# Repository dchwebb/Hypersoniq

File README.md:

# Hypersoniq
 Eurorack Polyphonic High Pass Filter

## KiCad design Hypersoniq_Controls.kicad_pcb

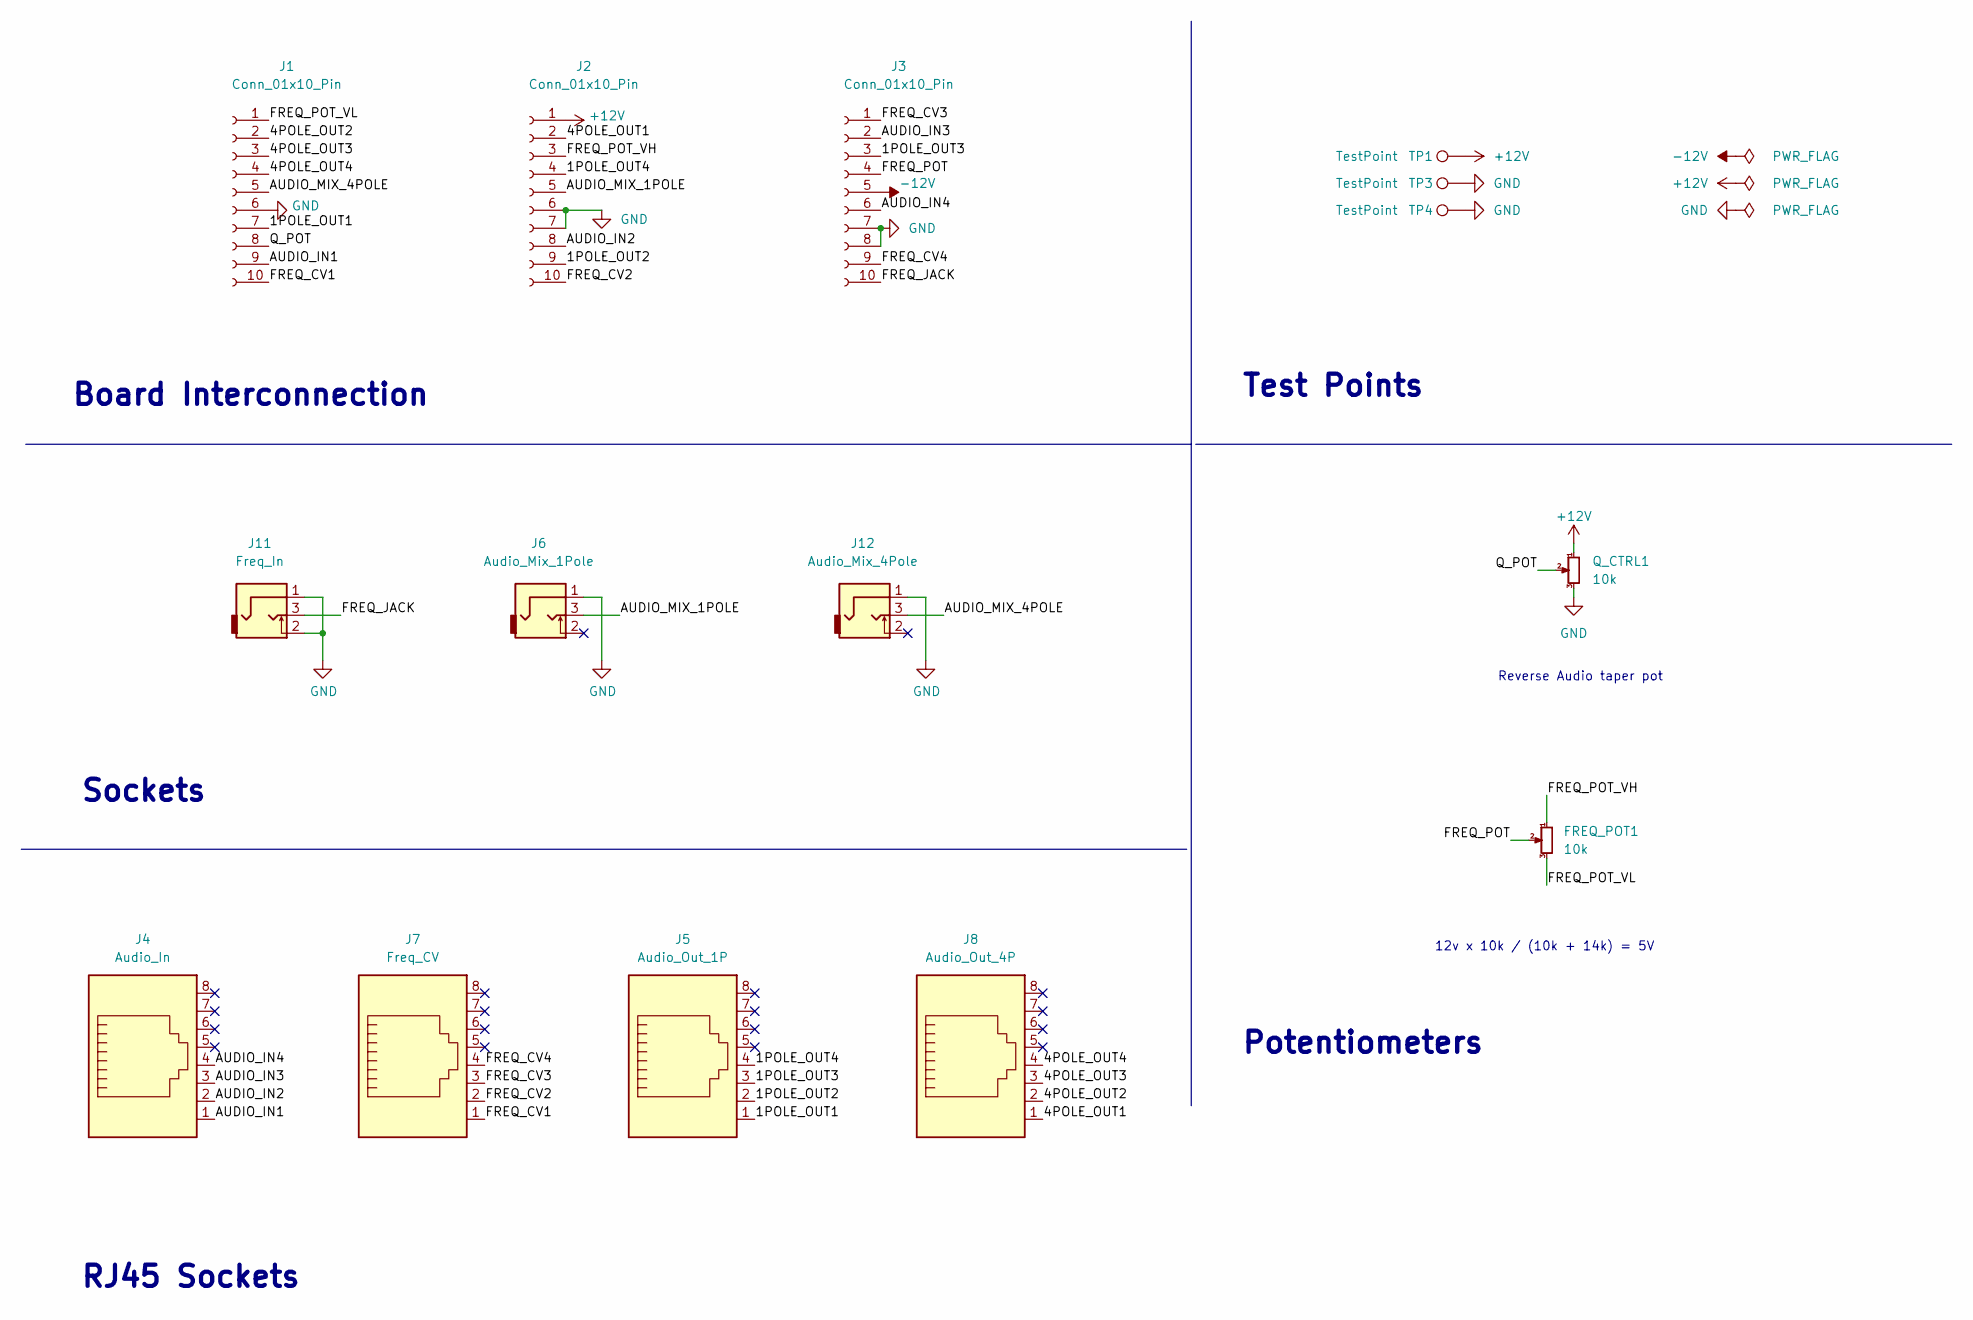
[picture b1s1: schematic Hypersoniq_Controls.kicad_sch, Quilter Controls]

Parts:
FREQ_POT1: 10k; Alpha_9mm_Potentiometer_Aligned
J1, J2, J3: Conn_01x10_Pin; PinSocket_1x10_P2.54mm_Vertical
J4: Audio_In; RJ45_Molex_42878-8506
J5: Audio_Out_1P; RJ45_Molex_42878-8506
J6: Audio_Mix_1Pole; THONKICONN_hole
J7: Freq_CV; RJ45_Molex_42878-8506
J8: Audio_Out_4P; RJ45_Molex_42878-8506
J11: Freq_In; THONKICONN_hole
J12: Audio_Mix_4Pole; THONKICONN_hole
Q_CTRL1: 10k; Alpha_9mm_Potentiometer_Aligned
TP1, TP3, TP4: TestPoint; 1.3mm_Test_Point

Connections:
+12V: J2.1, Q_CTRL1.1, TP1.1
-12V: J3.5
/1POLE_OUT1: J1.7, J5.1
/1POLE_OUT2: J2.9, J5.2
/1POLE_OUT3: J3.3, J5.3
/1POLE_OUT4: J2.4, J5.4
/4POLE_OUT1: J2.2, J8.1
/4POLE_OUT2: J1.2, J8.2
/4POLE_OUT3: J1.3, J8.3
/4POLE_OUT4: J1.4, J8.4
/AUDIO_IN1: J1.9, J4.1
/AUDIO_IN2: J2.8, J4.2
/AUDIO_IN3: J3.2, J4.3
/AUDIO_IN4: J3.6, J4.4
/AUDIO_MIX_1POLE: J2.5, J6.3
/AUDIO_MIX_4POLE: J1.5, J12.3
/FREQ_CV1: J1.10, J7.1
/FREQ_CV2: J2.10, J7.2
/FREQ_CV3: J3.1, J7.3
/FREQ_CV4: J3.9, J7.4
/FREQ_JACK: J3.10, J11.3
/FREQ_POT: FREQ_POT1.2, J3.4
/FREQ_POT_VH: FREQ_POT1.1, J2.3
/FREQ_POT_VL: FREQ_POT1.3, J1.1
/Q_POT: J1.8, Q_CTRL1.2
GND: J1.6, J2.6, J2.7, J3.7, J3.8, J6.1, J11.1, J11.2, J12.1, Q_CTRL1.3, TP3.1, TP4.1

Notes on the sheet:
RJ45 Sockets
Board Interconnection
Potentiometers
Sockets
Test Points
12v x 10k / (10k + 14k) = 5V
Reverse Audio taper pot

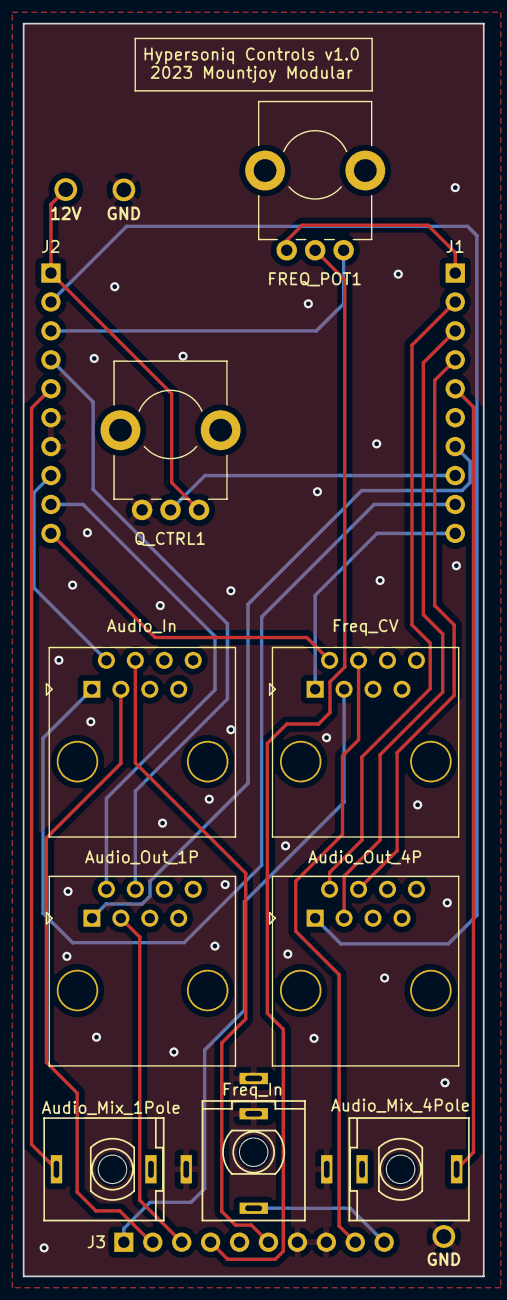
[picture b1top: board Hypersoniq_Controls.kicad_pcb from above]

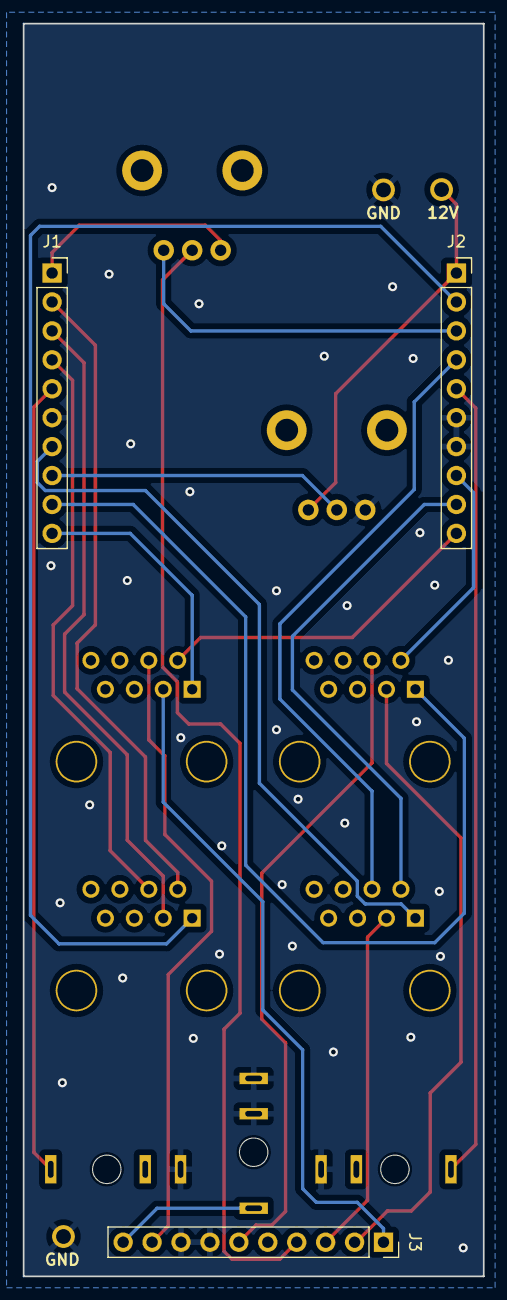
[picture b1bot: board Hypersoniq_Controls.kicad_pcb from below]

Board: 2 copper layers, 40.4 x 110.0 mm, 15 parts (3 on the bottom side), 25 nets.

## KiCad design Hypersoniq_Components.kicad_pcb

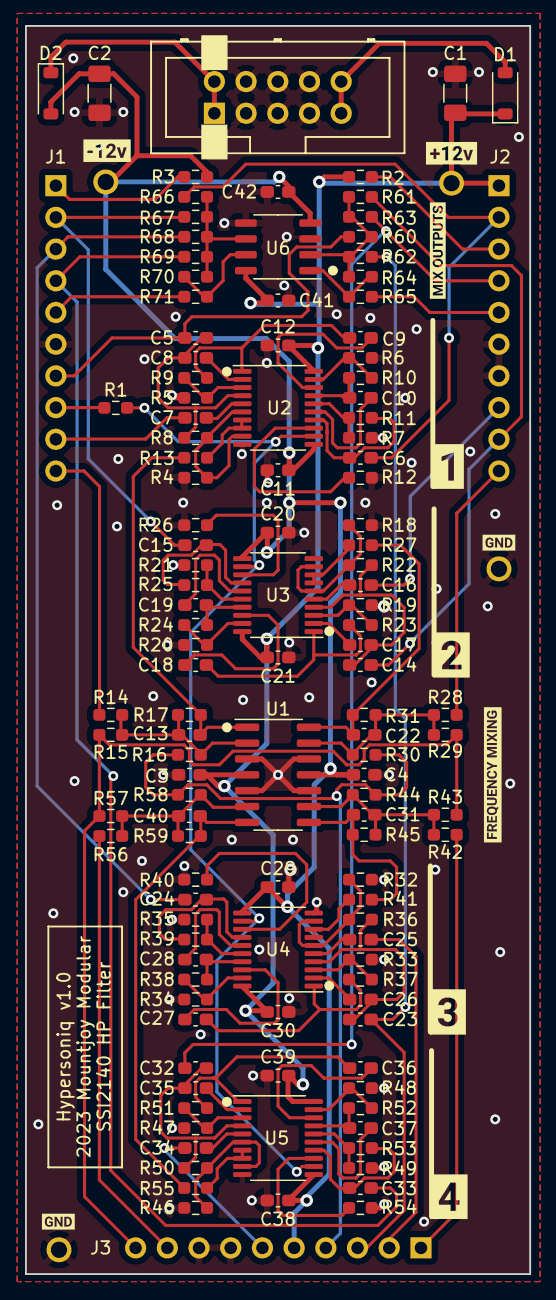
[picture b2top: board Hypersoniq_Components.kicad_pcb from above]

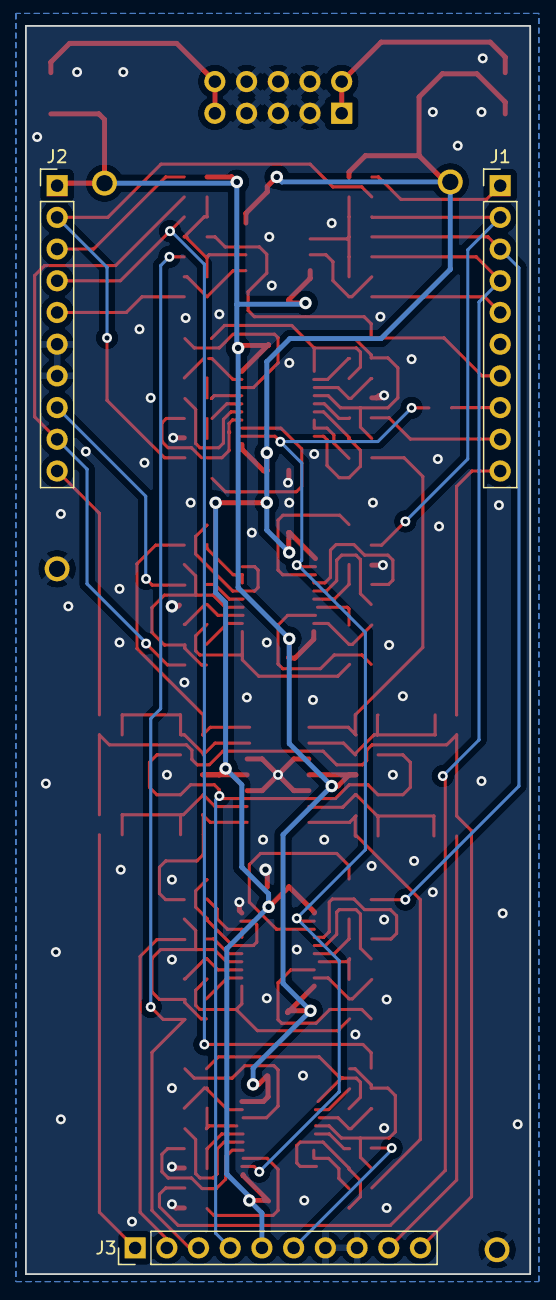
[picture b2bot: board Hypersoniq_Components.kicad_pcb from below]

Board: 2 copper layers, 40.4 x 100.0 mm, 139 parts (3 on the bottom side), 97 nets.

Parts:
C1, C2: 22uF; C_1206_3216Metric_Pad1.33x1.80mm_HandSolder
C3, C4, C11, C12, C20, C21, C29, C30, C38, C39, C41, C42: 100nF; C_0603_1608Metric_Pad1.08x0.95mm_HandSolder
C5, C6, C14, C15, C23, C24, C32, C33: 2.2nF; C_0603_1608Metric_Pad1.08x0.95mm_HandSolder
C7, C8, C9, C10, C16, C17, C18, C19, C25, C26, C27, C28, C34, C35, C36, C37: 1nF; C_0603_1608Metric_Pad1.08x0.95mm_HandSolder
C13, C22, C31, C40: 10nF; C_0603_1608Metric_Pad1.08x0.95mm_HandSolder
D1, D2: 1N5819; D_SOD-123
J1, J2, J3: Conn_01x10_Pin; PinHeader_1x10_P2.54mm_Vertical
J4: Eurorack_10_pin_power; Eurorack_10_pin_header
R1: 39k; R_0603_1608Metric_Pad0.98x0.95mm_HandSolder
R2: 8.2k; R_0603_1608Metric_Pad0.98x0.95mm_HandSolder
R3: 3.9k; R_0603_1608Metric_Pad0.98x0.95mm_HandSolder
R4, R5, R6, R7, R18, R19, R20, R21, R32, R33, R34, R35, R46, R47, R48, R49: 200; R_0603_1608Metric_Pad0.98x0.95mm_HandSolder
R8, R9, R10, R11, R22, R23, R24, R25, R36, R37, R38, R39, R50, R51, R52, R53, R60, R61, R62, R63, R66, R67, R68, R69: 10k; R_0603_1608Metric_Pad0.98x0.95mm_HandSolder
R12, R26, R40, R54, R65, R71: 1k; R_0603_1608Metric_Pad0.98x0.95mm_HandSolder
R13, R27, R41, R55: 56k; R_0603_1608Metric_Pad0.98x0.95mm_HandSolder
R14, R15, R16, R28, R29, R30, R42, R43, R44, R56, R57, R58: 100k; R_0603_1608Metric_Pad0.98x0.95mm_HandSolder
R17, R31, R45, R59: 150k; R_0603_1608Metric_Pad0.98x0.95mm_HandSolder
R64, R70: 4.7k; R_0603_1608Metric_Pad0.98x0.95mm_HandSolder
TP1, TP2, TP3, TP4: TestPoint; 1.3mm_Test_Point
U1: TL074; SOIC-14_3.9x8.7mm_P1.27mm
U2, U3, U4, U5: SSI2140; TSSOP-20_4.4x6.5mm_P0.65mm
U6: TL072; SO-8_3.9x4.9mm_P1.27mm
kibuzzard-64BBE4CA: G***; kibuzzard-64BBE4CA
kibuzzard-64BBF5E4: G***; kibuzzard-64BBF5E4
kibuzzard-64BBF56E: G***; kibuzzard-64BBF56E
kibuzzard-64BBF60A: G***; kibuzzard-64BBF60A
kibuzzard-64BBF567: G***; kibuzzard-64BBF567
kibuzzard-64BBF574: G***; kibuzzard-64BBF574
kibuzzard-64BBF597: G***; kibuzzard-64BBF597
kibuzzard-64BE60E0: G***; kibuzzard-64BE60E0
kibuzzard-640237DF, kibuzzard-640237DF#2: G***; kibuzzard-640237DF

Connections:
+12V: C1.1, C3.1, C12.1, C21.1, C30.1, C39.1, C41.1, D1.1 (K), J2.1, R2.1, TP1.1, U1.4 (V+), U2.20 (V+), U3.20 (V+), U4.20 (V+), U5.20 (V+), U6.8 (V+)
-12V: C2.2, C4.1, C11.1, C20.1, C29.1, C38.1, C42.1, D2.2 (A), J3.5, R3.2, TP2.1, U1.11 (V-), U2.11 (V-), U3.11 (V-), U4.11 (V-), U5.11 (V-), U6.4 (V-)
/1POLE_OUT1: C5.2, J1.7, R60.2
/1POLE_OUT2: C14.2, J2.9, R61.2
/1POLE_OUT3: C23.2, J3.3, R62.2
/1POLE_OUT4: C32.2, J2.4, R63.2
/4POLE_OUT1: C6.1, J2.2, R66.2
/4POLE_OUT2: C15.1, J1.2, R67.2
/4POLE_OUT3: C24.1, J1.3, R68.2
/4POLE_OUT4: C33.1, J1.4, R69.2
/+12V_IN: D1.2 (A), J4.9, J4.10
/-12V_IN: D2.1 (K), J4.1, J4.2
/AUDIO_IN1: C7.1, J1.9
/AUDIO_IN2: C16.1, J2.8
/AUDIO_IN3: C25.1, J3.2
/AUDIO_IN4: C34.1, J3.6
/AUDIO_MIX_1POLE: J2.5, R65.2
/AUDIO_MIX_4POLE: J1.5, R71.2
/FREQ_CV1: J1.10, R14.2
/FREQ_CV2: J2.10, R28.2
/FREQ_CV3: J3.1, R42.2
/FREQ_CV4: J3.9, R56.2
/FREQ_JACK: J3.10, R15.2, R29.2, R43.2, R57.2
/FREQ_POT: J3.4, R16.2, R30.2, R44.2, R58.2
/FREQ_POT_VH: J2.3, R2.2
/FREQ_POT_VL: J1.1, R3.1
/Filter_Voice1/FREQ_CONTROL: C13.2, R13.2, R17.1, U1.1
/Filter_Voice1/Q_FEEDBACK: R4.1, R8.2, U2.6, U2.9
/Filter_Voice2/FREQ_CONTROL: C22.2, R27.2, R31.1, U1.14
/Filter_Voice2/Q_FEEDBACK: R18.1, R22.2, U3.6, U3.9
/Filter_Voice3/FREQ_CONTROL: C31.2, R41.2, R45.1, U1.8
/Filter_Voice3/Q_FEEDBACK: R32.1, R36.2, U4.6, U4.9
/Filter_Voice4/FREQ_CONTROL: C40.2, R55.2, R59.1, U1.7
/Filter_Voice4/Q_FEEDBACK: R46.1, R50.2, U5.6, U5.9
/Q_CONTROL: R1.2, U2.12, U3.12, U4.12, U5.12
/Q_POT: J1.8, R1.1
GND: C1.2, C2.1, C3.2, C4.2, C11.2, C12.2, C20.2, C21.2, C29.2, C30.2, C38.2, C39.2, C41.2, C42.2, J1.6, J2.6, J2.7, J3.7, J3.8, J4.3, J4.4, J4.5, J4.6, J4.7, J4.8, R4.2, R5.2, R6.2, R7.2, R12.2, R18.2, R19.2, R20.2, R21.2, R26.2, R32.2, R33.2, R34.2, R35.2, R40.2, R46.2, R47.2, R48.2, R49.2, R54.2, TP3.1, TP4.1, U1.3 (+), U1.5 (+), U1.10 (+), U1.12 (+), U2.10 (GND), U3.10 (GND), U4.10 (GND), U5.10 (GND), U6.3 (+), U6.5 (+)
unnamed: C5.1, C8.1, R8.1, U2.4
unnamed: C6.2, R11.1, U2.14
unnamed: C7.2, U2.5
unnamed: C8.2, U2.2
unnamed: C9.1, R9.1, U2.1
unnamed: C9.2, U2.18
unnamed: C10.1, R10.1, U2.17
unnamed: C10.2, U2.15
unnamed: C14.1, C17.1, R22.1, U3.4
unnamed: C15.2, R25.1, U3.14
unnamed: C16.2, U3.5
unnamed: C17.2, U3.2
unnamed: C18.1, R23.1, U3.1
unnamed: C18.2, U3.18
unnamed: C19.1, R24.1, U3.17
unnamed: C19.2, U3.15
unnamed: C23.1, C26.1, R36.1, U4.4
unnamed: C24.2, R39.1, U4.14
unnamed: C25.2, U4.5
unnamed: C26.2, U4.2
unnamed: C27.1, R37.1, U4.1
unnamed: C27.2, U4.18
unnamed: C28.1, R38.1, U4.17
unnamed: C28.2, U4.15
unnamed: C32.1, C35.1, R50.1, U5.4
unnamed: C33.2, R53.1, U5.14
unnamed: C34.2, U5.5
unnamed: C35.2, U5.2
unnamed: C36.1, R51.1, U5.1
unnamed: C36.2, U5.18
unnamed: C37.1, R52.1, U5.17
unnamed: C37.2, U5.15
unnamed: R5.1, R9.2, U2.3
unnamed: R6.1, R10.2, U2.19
unnamed: R7.1, R11.2, U2.16
unnamed: R12.1, U2.13
unnamed: R19.1, R23.2, U3.3
unnamed: R20.1, R24.2, U3.19
unnamed: R21.1, R25.2, U3.16
unnamed: R26.1, U3.13
unnamed: R33.1, R37.2, U4.3
unnamed: R34.1, R38.2, U4.19
unnamed: R35.1, R39.2, U4.16
unnamed: R40.1, U4.13
unnamed: R47.1, R51.2, U5.3
unnamed: R48.1, R52.2, U5.19
unnamed: R49.1, R53.2, U5.16
unnamed: R54.1, U5.13
unnamed: R64.1, R65.1, U6.1
unnamed: R70.1, R71.1, U6.7
unnamed: C13.1, R14.1, R15.1, R16.1, R17.2, U1.2 (-)
unnamed: C40.1, R56.1, R57.1, R58.1, R59.2, U1.6 (-)
unnamed: C31.1, R42.1, R43.1, R44.1, R45.2, U1.9 (-)
unnamed: C22.1, R28.1, R29.1, R30.1, R31.2, U1.13 (-)
unnamed: R13.1, U2.7 (EXPO_CTL), U2.8 (TEMPCO)
unnamed: R27.1, U3.7 (EXPO_CTL), U3.8 (TEMPCO)
unnamed: R41.1, U4.7 (EXPO_CTL), U4.8 (TEMPCO)
unnamed: R55.1, U5.7 (EXPO_CTL), U5.8 (TEMPCO)
unnamed: R60.1, R61.1, R62.1, R63.1, R64.2, U6.2 (-)
unnamed: R66.1, R67.1, R68.1, R69.1, R70.2, U6.6 (-)

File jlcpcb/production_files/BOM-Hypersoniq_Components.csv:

Comment,Designator,Footprint,LCSC
22uF,"C1,C2",C_1206_3216Metric_Pad1.33x1.80mm_HandSolder,C12891
100nF,"C11,C12,C20,C21,C29,C3,C30,C38,C39,C4,C41,C42",C_0603_1608Metric_Pad1.08x0.95mm_HandSolder,C14663
1nF,"C10,C16,C17,C18,C19,C25,C26,C27,C28,C34,C35,C36,C37,C7,C8,C9",C_0603_1608Metric_Pad1.08x0.95mm_HandSolder,C1588
2.2nF,"C14,C15,C23,C24,C32,C33,C5,C6",C_0603_1608Metric_Pad1.08x0.95mm_HandSolder,C1604
1k,"R12,R26,R40,R54,R65,R71",R_0603_1608Metric_Pad0.98x0.95mm_HandSolder,C21190
150k,"R17,R31,R45,R59",R_0603_1608Metric_Pad0.98x0.95mm_HandSolder,C22807
3.9k,R3,R_0603_1608Metric_Pad0.98x0.95mm_HandSolder,C23018
39k,R1,R_0603_1608Metric_Pad0.98x0.95mm_HandSolder,C23153
4.7k,"R64,R70",R_0603_1608Metric_Pad0.98x0.95mm_HandSolder,C23162
56k,"R13,R27,R41,R55",R_0603_1608Metric_Pad0.98x0.95mm_HandSolder,C23206
100k,"R14,R15,R16,R28,R29,R30,R42,R43,R44,R56,R57,R58",R_0603_1608Metric_Pad0.98x0.95mm_HandSolder,C25803
10k,"R10,R11,R22,R23,R24,R25,R36,R37,R38,R39,R50,R51,R52,R53,R60,R61,R62,R63,R66,R67,R68,R69,R8,R9",R_0603_1608Metric_Pad0.98x0.95mm_HandSolder,C25804
8.2k,R2,R_0603_1608Metric_Pad0.98x0.95mm_HandSolder,C25981
10nF,"C13,C22,C31,C40",C_0603_1608Metric_Pad1.08x0.95mm_HandSolder,C57112
TL072,U6,SO-8_3.9x4.9mm_P1.27mm,C6961
200,"R18,R19,R20,R21,R32,R33,R34,R35,R4,R46,R47,R48,R49,R5,R6,R7",R_0603_1608Metric_Pad0.98x0.95mm_HandSolder,C8218
1N5819,"D1,D2",D_SOD-123,C8598

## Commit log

2023-07-19 First draft of schematic
2023-07-22 PCB Layout
2023-07-22 Revert "PCB Layout"
    This reverts commit f9e64c4088f3b37948fb3949196b7229d7a48ca0.
2023-07-22 Revert "Revert "PCB Layout""
    This reverts commit 17ea893c43406ccb0184a474adf0eed468bf1595.
2023-07-22 First draft of PCB layout complete
2023-07-23 Controls PCB lay out
2023-07-23 Started laying out Panel
2023-07-24 Started generating JLC placement details
2023-07-24 Minor cleanup
2023-07-25 Panel and Control tidy up
2023-07-25 Updated SSI2149 symbol; cleaned up routing on component board
2023-07-26 Updated SSI2140 footprints
2023-07-27 v1.0 Design sent for manufacture
2023-08-12 Added v1.0 component schematic pdf
2023-09-14 Minor changes
